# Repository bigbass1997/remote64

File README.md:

## Description
This project enables N64 homebrew developers to test their roms on real hardware, without actually owning said hardware.

Project is split in two parts: the server which handles all incoming requests, performs them on hardware, and sends back
what happened; and the client which is what developers use to test their roms.

The server side can be run by anyone that has a compatible hardware setup. It manages incomming requests for testing,
captures the console's output, and relays that information back to the client. Servers may have a varying set of
capabilities. If the client requests a feature the server doesn't support, the user will be notified.

If a client connects while another test is in progress, the new client will be placed in a queue and automatically
serviced once the current test has finished. The maximum length of a test is defined by the server, but will likely
be quite generous.

## Why does this exist?
Ultimately, this is an attempt to reduce the cost of entry into N64 homebrew and research. Especially given the chip
shortage and other circumstances that have severely limited flashcart production.

While it is possible to ask others to test a rom build, it's also possible that no one will be available when needed.
This is _not_ intended to completely replace developers purchasing their own flashcarts/consoles, nor to replace community
testers; rather it is here to supplement those testing methods.

## Which server should I connect to?
**TODO**

## Server Capabilities
The bare minimum a server setup requires is some method to automatically upload and start the provided ROM image, and a
capture device to record the video output with. The server software will not work without a valid video stream, even if
live playback isn't enabled.

Optional capabilities include:
- Live playback (requires decent upload speed)
- Audio recording (for final recording, and live playback if enabled)
- Controller input (requires live playback and input passthrough)

## Repo Structure
`/client/`, `/common/`, and `/server/` make up the software side, while `/controller/` contains the hardware used by the
server for powering the system on/off, and passing in controller inputs.

`/docker/` contains container build script(s) that can be used for cross-compiling.

## Compiling/Building
If you wish to build from source, for your own system, Rust is integrated with the `cargo` build system. To install Rust and `cargo`, just follow [these instructions](https://doc.rust-lang.org/cargo/getting-started/installation.html). Once installed, while in the project's root directory, run `cargo build --bin remote64-client --release` to build (use `--bin remote64-server` for server builds), or use `cargo run --bin remote64-client --release` to run directly. The built binary will be available in `./target/release/`

To cross-compile builds for other operating systems, you can use [rust-embedded/cross](https://github.com/rust-embedded/cross).

The `Cross.toml` file is configured to expect a local docker container for linux and windows builds.

#### Linux
Docker: `docker build -t remote64-image-linux:tag docker/linux/`  
Rust: `cross build --target x86_64-unknown-linux-gnu --bin remote64-client --release`

#### Windows
Docker: `docker build -t remote64-image-windows:tag docker/windows/`  
Rust: `cross build --target x86_64-pc-windows-gnu --bin remote64-client --release`  
_Note: Cross-compiling for windows is currently broken. I cannot get the container to recognize the portaudio library._

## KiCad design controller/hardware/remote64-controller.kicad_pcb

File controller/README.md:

### Description
This is the hardware side of the remote64 project, to enable remote control of a Nintendo 64 console.

The board uses a PIC18F47K42 microcontroller to handle controller input passthrough, via a USB/UART bridge. It also controls two relays which can be hooked up to the power switch of the N64, to remotely power the console on/off as needed.

### Discord/Support
If you have questions, you can find me on the [N64brew Discord server](https://discord.gg/WqFgNWf).

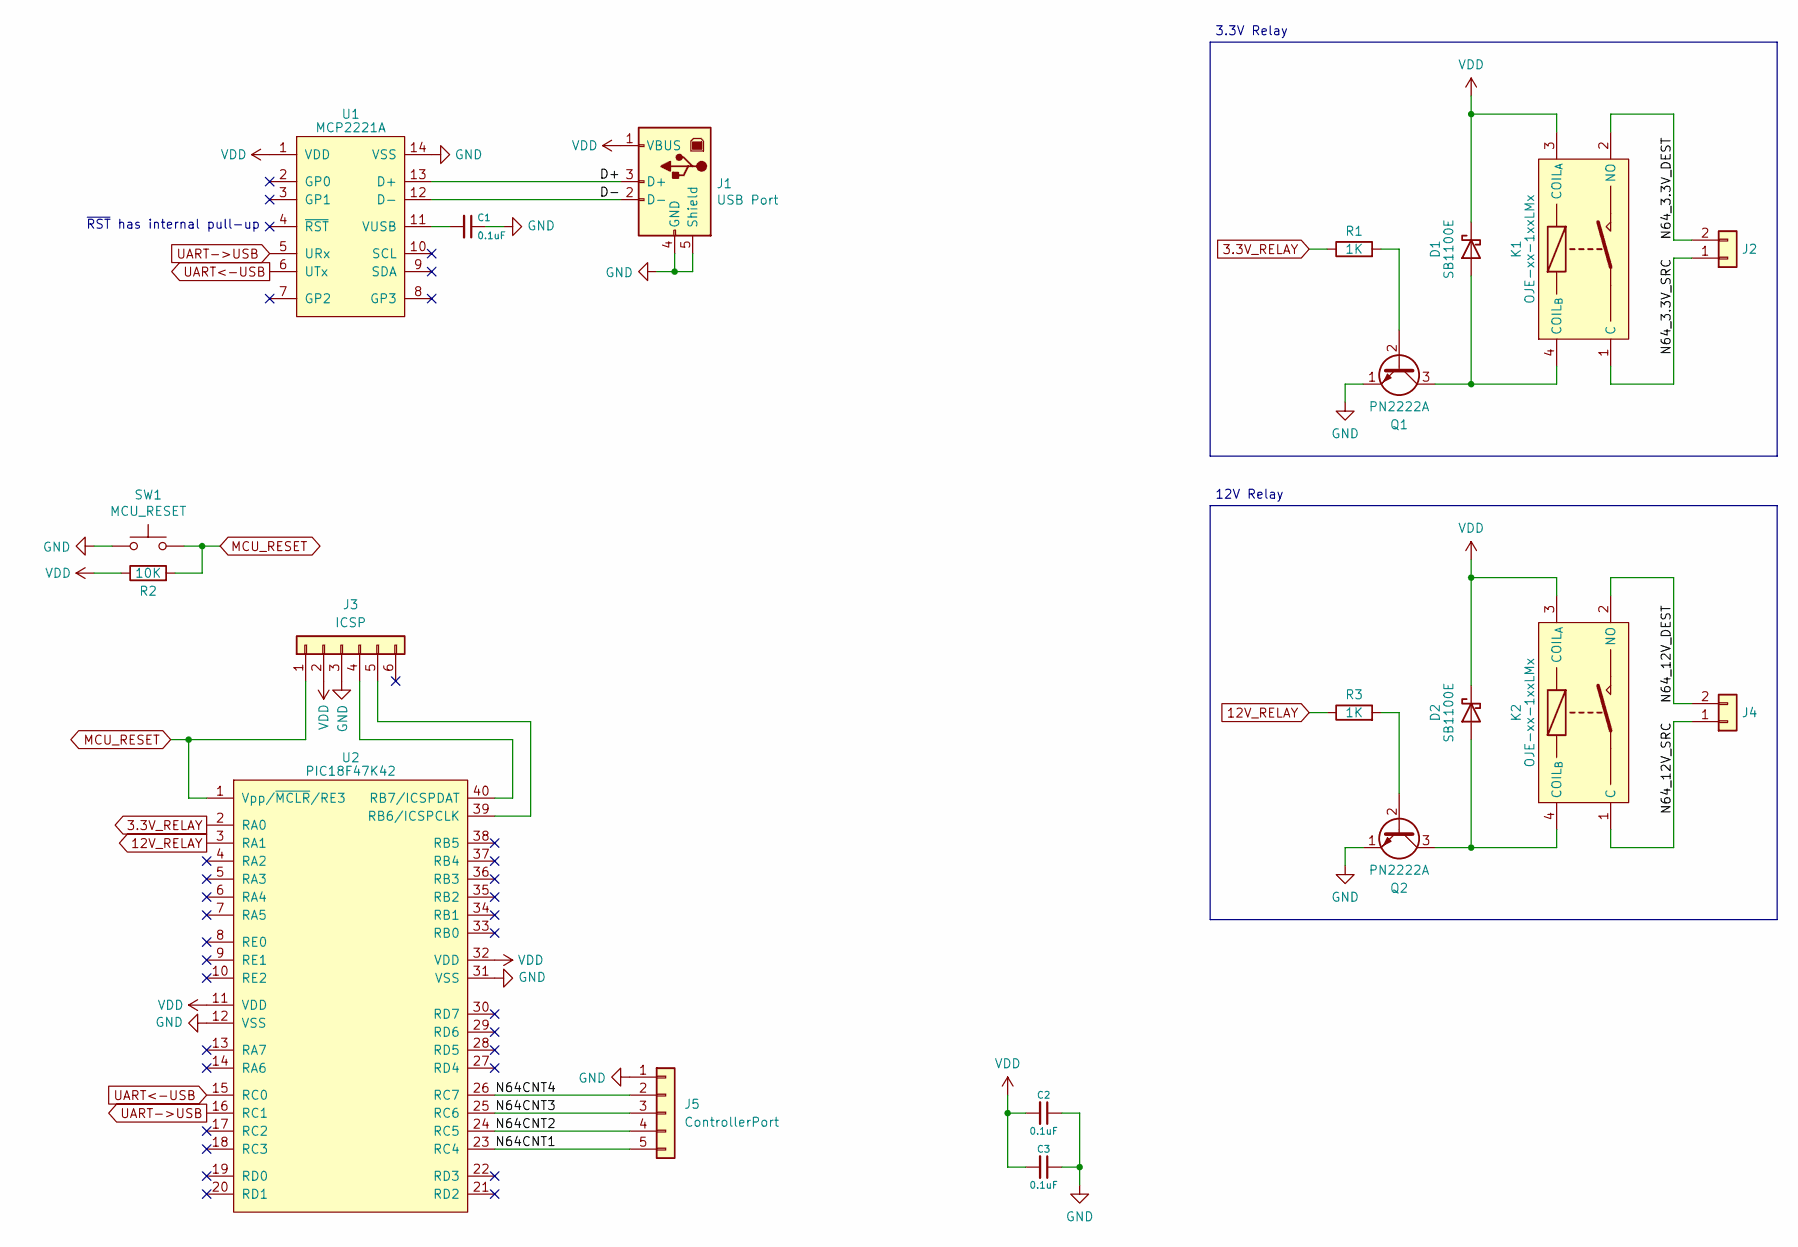
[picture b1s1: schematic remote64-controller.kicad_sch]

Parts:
C1, C2, C3: 0.1uF; C_Disc_D3.4mm_W2.1mm_P2.50mm
D1, D2: SB1100E; D_DO-41_SOD81_P10.16mm_Horizontal
J1: USB Port; USB_B_OST_USB-B1HSxx_Horizontal
J2, J4: Conn_01x02; TerminalBlock_Phoenix_PT-1,5-2-5.0-H_1x02_P5.00mm_Horizontal
J3: ICSP; PinHeader_1x06_P2.54mm_Vertical
J5: ControllerPort; PinHeader_1x05_P2.54mm_Vertical
K1, K2: OJE-xx-1xxLMx; OJE-SS-105LMH
Q1, Q2: PN2222A; TO-92_Inline
R1, R3: 1K; R_Axial_DIN0207_L6.3mm_D2.5mm_P10.16mm_Horizontal
R2: 10K; R_Axial_DIN0207_L6.3mm_D2.5mm_P10.16mm_Horizontal
SW1: MCU_RESET; SW_PUSH_6mm_H7.3mm
U1: MCP2221A; DIP-14_W7.62mm
U2: PIC18F47K42; DIP-40_W15.24mm

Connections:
3.3V_RELAY: R1.1, U2.2 (RA0)
12V_RELAY: R3.1, U2.3 (RA1)
/D+: J1.3 (D+), U1.13 (D+)
/D-: J1.2 (D-), U1.12 (D-)
/N64CNT1: J5.5, U2.23 (RC4)
/N64CNT2: J5.4, U2.24 (RC5)
/N64CNT3: J5.3, U2.25 (RC6)
/N64CNT4: J5.2, U2.26 (RC7)
/N64_3.3V_DEST: J2.2, K1.2 (NO)
/N64_3.3V_SRC: J2.1, K1.1 (C)
/N64_12V_DEST: J4.2, K2.2 (NO)
/N64_12V_SRC: J4.1, K2.1 (C)
GND: C1.1, C2.1, C3.1, J1.4 (GND), J1.5 (Shield), J3.3, J5.1, Q1.1 (E), Q2.1 (E), SW1.1, U1.14 (VSS), U2.12 (VSS), U2.31 (VSS)
MCU_RESET: J3.1, R2.2, SW1.2, U2.1 (Vpp/~MCLR/RE3)
unnamed: C1.2, U1.11 (VUSB)
unnamed: D1.2 (A), K1.4 (COIL_{B}), Q1.3 (C)
unnamed: D2.2 (A), K2.4 (COIL_{B}), Q2.3 (C)
unnamed: J3.4, U2.40 (RB7/ICSPDAT)
unnamed: J3.5, U2.39 (RB6/ICSPCLK)
unnamed: Q1.2 (B), R1.2
unnamed: Q2.2 (B), R3.2
UART->USB: U1.5 (URx), U2.16 (RC1)
UART<-USB: U1.6 (UTx), U2.15 (RC0)
VDD: C2.2, C3.2, D1.1 (K), D2.1 (K), J1.1 (VBUS), J3.2, K1.3 (COIL_{A}), K2.3 (COIL_{A}), R2.1, U1.1 (VDD), U2.11 (VDD), U2.32 (VDD)

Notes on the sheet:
3.3V Relay
~{RST} has internal pull-up
12V Relay

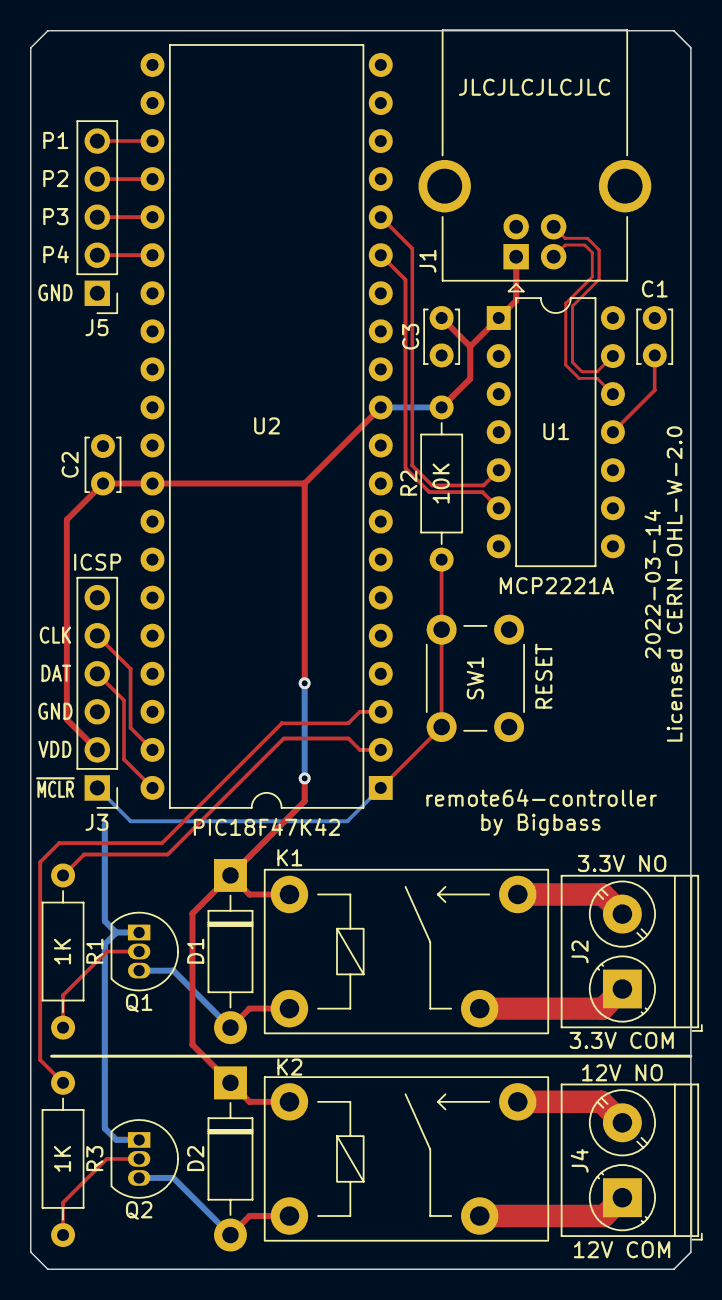
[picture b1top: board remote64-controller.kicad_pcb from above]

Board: 2 copper layers, 44.1 x 82.7 mm, 20 parts (0 on the bottom side), 24 nets.

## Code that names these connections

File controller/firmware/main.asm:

    include "p18f47k42.inc"
    include "macros.inc"
    processor 18f47k42
    
    CONFIG WDTE = OFF
   ; CONFIG DEBUG = ON
    CONFIG LVP = ON
    CONFIG MCLRE = EXTMCLR
    CONFIG MVECEN = ON ; Enables Interrupt Vector Table ; IVTBASE + 2*(vector number)
    
    CONFIG RSTOSC = HFINTOSC_64MHZ
    CONFIG FEXTOSC = OFF
    CONFIG CLKOUTEN = OFF
    
    CONFIG XINST = ON
    
ResVec	    code    0x0000
    goto    Setup
    
U1RXVec	    code    0x003E  ; (0x0008 + (2 * 27))
    dw	    (0x0100>>2)
    
	    code	0x0600
; === Look at bottom of file for ISR routines ===
    
; === DEFINE PINS (text substitutions) ===
; refer to pinout documentation for more information
#define	    RELAY12	    LATA, 1
#define	    RELAY3	    LATA, 0

#define	    N64CNT4	    PORTC, 7
#define	    N64CNT3	    PORTC, 6
#define	    N64CNT2	    PORTC, 5
#define	    N64CNT1	    PORTC, 4

#define	    N64CNT4_LAT	    LATC, 7
#define	    N64CNT3_LAT	    LATC, 6
#define	    N64CNT2_LAT	    LATC, 5
#define	    N64CNT1_LAT	    LATC, 4

#define	    N64CNT4_TRIS    TRISC, 7
#define	    N64CNT3_TRIS    TRISC, 6
#define	    N64CNT2_TRIS    TRISC, 5
#define	    N64CNT1_TRIS    TRISC, 4




; === REGISTERS ===
; ACCESS BANK  (0x00 - 0x5F)
ZEROS_REG       equ H'00' ; Always 0x00
ONES_REG        equ H'01' ; Always 0xFF

; 0x02 - 0x0D unused

UTIL_FLAGS      equ H'0E' ; Utility Flags, initalized with 0x00
; <7:0> Unused

; Pause Clock
PAUSE_REG_0     equ H'10'
PAUSE_REG_1     equ H'11'
PAUSE_REG_2     equ H'12'

PAUSE_TMP_0     equ H'13'
PAUSE_TMP_1     equ H'14'
PAUSE_TMP_2     equ H'15'

; Auxillary Loop Counters
LOOP_COUNT_0    equ H'16'
LOOP_COUNT_1    equ H'17'


JUNK_REG        equ H'5F'

; BANK 0  (0x60 - 0xFF)

; BANK 1

; BANK 2



; === CONSTANT BYTES ===
USB_CMD_PING        equ H'01'
USB_CMD_ON	    equ H'02'
USB_CMD_OFF	    equ H'03'


; COMMON SUBROUTINES (may also contain macros) ;
    include "sub-utilities.inc"
    include "usb-handling.inc"
    
; Initialize device ;
Setup:
    include "startup.inc"
    
    movlb   B'000000'
    
;;;;;====================== Main Loop Start ======================;;;;;
Start:
    nop
    goto    Start
    
    
    
; INTERRUPT SUBROUTINES ;
    
U1RXISR	    code    0x0100
    BANKSEL PIR0
    bcf	    PIE3, U1RXIE
U1RXISR_Continue:
    movffl  U1RXB, WREG
    movlb   B'000000'
    movwf   JUNK_REG
    
    xorlw   USB_CMD_PING
    btfsc   STATUS, Z
    call    USBRX_Ping
    movf    JUNK_REG, 0
    
    xorlw   USB_CMD_ON
    btfsc   STATUS, Z
    call    USBRX_On
    movf    JUNK_REG, 0
    
    xorlw   USB_CMD_OFF
    btfsc   STATUS, Z
    call    USBRX_Off
    movf    JUNK_REG, 0
    
    BANKSEL PIR0
    btfsc   PIR3, U1RXIF
    goto    U1RXISR_Continue	; if buffer not empty, keep processing
    
    bsf	    PIE3, U1RXIE
    retfie
    
    
    end

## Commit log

2022-03-02 Initial commit.
2022-03-07 Revised README.
2022-03-07 Implemented better logging and fixed up socket connect/disconnect logic.
2022-03-07 Merged redundant code so that there is no explicit "active" client, but rather just whatever client is at the front of the queue. Added some comments and queue req/res packet types.
2022-03-07 Added socket close handling for when the server cuts the connection.
2022-03-16 Added controller hardware.
2022-03-16 Updated README and docker files.
2022-03-16 Improved logging and implemented basic audio streaming. Began cleaning and reorganizing code.
2022-03-16 Updated Cross.toml with new docker configuration.
2022-03-16 Adjusted README formatting.
2022-03-16 Updated hardware .gitignore
2022-03-17 Fixed typo in client clap command.
2022-04-09 Added internal multi-thread communication. Reorganized video stream and audio/video recording.
2022-04-09 Added remote64-controller firmware source.
2022-04-09 Removed temporary test code.
2022-04-09 Migrated to using newly implemented BroadcastNetwork for internal message passing. Changed "capabilities" terminology to "features".
2022-04-09 Added video encoding, and automatic clearing of temporally recorded data.
2022-04-09 Fixed client queue processing bugs.
2022-04-11 Combined video and audio data into a single frame object/packet. Moved video decoding/encoding to frame (de)serialization methods.
2022-04-11 Moved inter-communication structs/logic to common.
2022-04-11 Temporary commit, this code is broken.
2022-04-12 Rewrote the TCP network code; removed dependency on broken websocket crate. Added basic frame buffering to avoid latency issues, at the cost of 3-5 seconds of delay.
2022-04-21 Added close packet. Split TCP sender/receiver into separate threads.
2022-04-24 Cleaned up old/unused code.
2022-04-24 Changed client to use cpal for audio.

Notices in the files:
README.md:
License: BSD 2-Clause
License: CERN OHL-W-V2
controller/hardware/remote64-controller.kicad_pcb:
Licensed CERN-OHL-W-2.0
